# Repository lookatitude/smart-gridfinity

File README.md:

# Smart Gridfinity

**A smart storage system built on Gridfinity: it knows where every bin is, and it can point
to the one you need.**

[Gridfinity](https://gridfinity.xyz/) is an open, modular storage standard: a 42 mm grid of
baseplates and bins that you print yourself. Smart Gridfinity keeps that standard and adds
two things to it:

- **Location tracking.** Every bin carries a small ID chip. The base reads which bin stands
  on which cell, so the system always has a current map of your storage. Move a bin, or
  rearrange the whole grid, and the map follows without any setup.
- **Signalling.** Every compartment has a light under a clear floor. Ask your software, or
  an AI agent, for a part and the compartment that holds it lights up.

Around those two ideas the design aims for:

- **Bins that stay simple.** No battery, no radio and no processor in a bin. It gets power
  and data through four contacts in its foot, and works at any quarter turn.
- **A grid that grows.** Tiles snap together edge to edge and discover their neighbours.
  One power feed runs many tiles, flat on a desk or on a wall with magnets.
- **Optional smartness.** Plain Gridfinity bins and baseplates still fit and are included.
  Powered parts are an addition, not a requirement.
- **No soldering at the printed parts.** The circuit boards arrive assembled and plug or
  screw in.

Everything is open source: the OpenSCAD models, the circuit boards (KiCad, generated from
Python), and the checks that keep the two in agreement.

**Status: design stage.** The models, boards and checks agree with each other, but nothing
has been printed, no board has been ordered or reviewed by a person, and there is no
firmware or software yet.

## Explore

| Start here | |
|---|---|
| **[How it works](docs/how-it-works.md)** | The whole system explained with pictures, in about ten minutes |
| [Parts guide](docs/parts-guide.md) | Every printed part and board, which file makes it, how to print |
| [Status and open questions](docs/status.md) | What has been checked, and what has not |
| [Glossary](docs/glossary.md) | Tile, cell, row board, power cell and the rest |
| [Illustrated design page](https://lookatitude.github.io/smart-gridfinity/smart/design.html) | The full design on one page, with diagrams |
| [All documentation](docs/README.md) | Index by what you want to do |

## What is in the repository

| Folder | Contents |
|---|---|
| `lib/`, `parts/` | OpenSCAD sources: plain baseplates and bins, smart tiles, smart bins, power bin, drawer unit, jar sleeves, tile keys |
| `assembly.scad`, `assembly_smart.scad` | Assembled views used for the pictures |
| `pcb/` | The five circuit boards as KiCad files, generated by Python scripts. See [`pcb/README.md`](pcb/README.md) |
| `tests/` | Design checks: fit, contacts, power, grid layout. See [`tests/README.md`](tests/README.md) |
| `docs/` | Documentation, the materials list and the illustrated design page |
| `tools/` | Helper scripts: `make_intro_gif.sh` builds the animation above from `assembly_intro.scad` |

## The smart system in four lines

- Bins have no radio and no processor: a round board in the foot has four contact rings, an
  ID chip and a connector for the bin's lights.
- Under every row of cells in a tile sits one board with spring pins. The first row's board
  has the radio module and a 5 V converter; further rows are joined by short flat cables.
- A power bin on a starter tile feeds 12–24 V into the grid and talks to your network.
- Tiles are 2×2 to 4×4 cells and join with printed keys and edge connectors, without screws.

The full walk-through is in [How it works](docs/how-it-works.md).

## Build

Needs OpenSCAD 2021.01 or newer. Printable files go to `build/`, which is not in the repository.

    ./build.sh          # plain parts
    ./build_smart.sh    # smart parts

Sized for a 256 mm print bed.

Ready-made STL files are attached to the [releases](https://github.com/lookatitude/smart-gridfinity/releases). They are untested.

## Checks

Needs Python 3, OpenSCAD and, for the boards, KiCad 10.

    tests/run_all.sh    # contacts, power, grid layout, fit (the fit checks take over 10 minutes)

See `pcb/README.md` for the board checks.

## Licence

MIT. See `LICENSE`. This covers the OpenSCAD models, the scripts and the board designs.

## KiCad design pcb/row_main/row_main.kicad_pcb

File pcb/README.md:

# Circuit boards

Five boards, defined in Python and written out as KiCad 10 projects. All are drafts: they pass
KiCad's rule checks, but no person has reviewed them and none has been built.

| Board | Where it goes | Layers |
|---|---|---|
| `bin_board` | In the foot of each smart bin: four contact rings, ID chip, connector for the lights | 2 |
| `row_main` | Under the first row of a tile: spring pins for four cells, radio module, 5 V converter, switch chips, one flat-cable socket | 4 |
| `row_strip` | Under every further row: spring pins for four cells, one switch chip, two flat-cable sockets. Can be snapped shorter | 2 |
| `feed_board` | Under the power cell of a starter tile: four feed pins | 2 |
| `power_board` | Inside the power bin: DC input, fuse, hub radio | 4 |

## Contacts

Each cell has four spring pins in a line from the cell centre: ID at 0 mm, light data at
5.4 mm, 5 V at 9.2 mm, ground at 12.9 mm. The bin board has matching concentric rings, so a
bin works at any quarter turn.

Rows are joined by a flat cable: 12 conductors, 0.5 mm pitch, 30 mm long, contacts on the same
side at both ends. Positions 1–12: 5V, 5V, GND, GND, light data, GND, ID, select 0, select 1,
and three row-enable lines that shift by one on each strip.

## Regenerating

    python3 boards.py                 # schematics, parts lists, library tables
    python3 layout_bin.py             # bin_board layout
    python3 layout_contact.py         # feed_board layout
    python3 layout_rows.py strip      # row_strip layout
    python3 layout_rows.py main --keep   # row_main layout from the saved routing (row_main.ses)
    python3 layout_power.py place && python3 layout_power.py route --keep   # power_board
    python3 outputs.py                # rule checks, pictures, bom.csv, fab/ for every board

`row_main` and `power_board` are routed with Freerouting. Its results are not repeatable, so
the routing that passed is saved as a `.ses` file next to each board.

## Checks

`grid_limits.py` and `grid_power.py` model how far one power feed reaches across a grid.

    python3 check_rows.py    # row boards against the printed tile: outline, pins, holes, sockets
    python3 signals.py       # signal levels and timing through the switch chips

Each board folder holds `erc.rpt` and `drc.rpt` from the last run.

## Known limits

- The flat-cable sockets allow 0.7 A at 5 V per cable, so firmware must hold full white to
  11 lights behind any one cable.
- On `row_main` the 5 V copper narrows to 0.8 mm at the cable socket and runs on inner layers.
- `row_main` is checked at 0.125 mm track spacing, the other boards at 0.15 mm.
- Snapping a `row_strip` shorter cuts through 5 V and ground copper 0.7 mm apart. Untested.

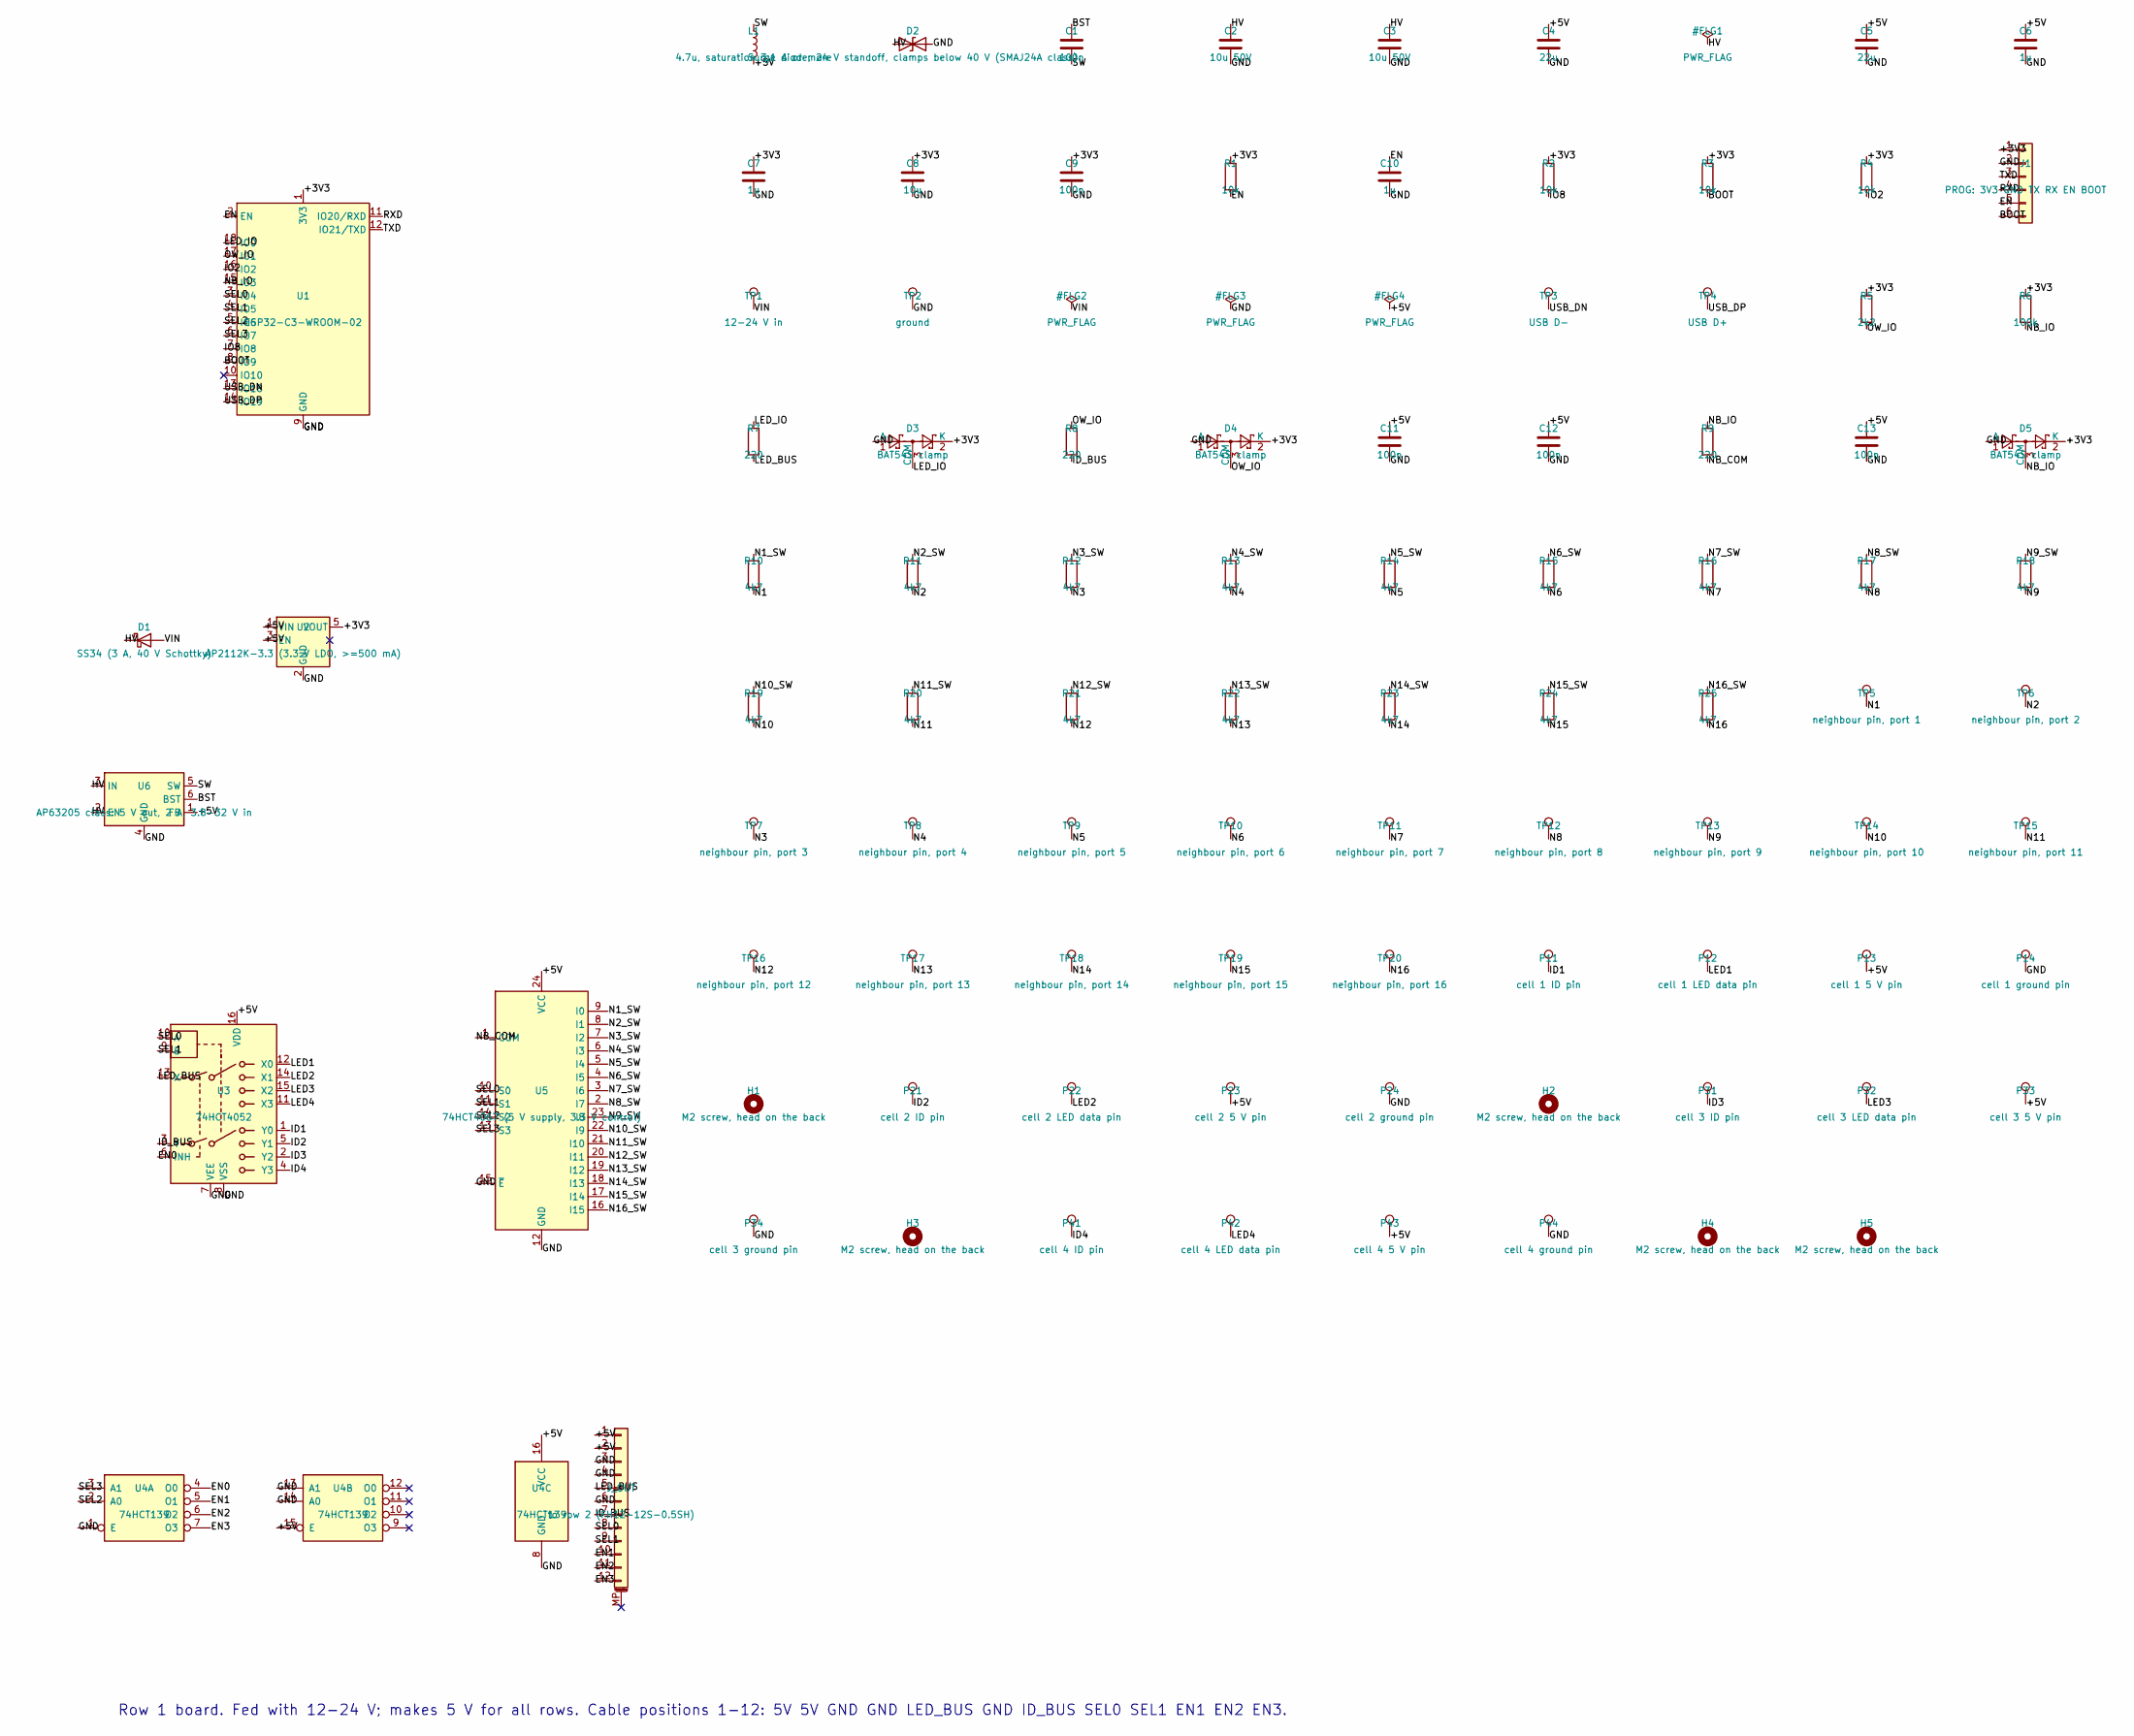
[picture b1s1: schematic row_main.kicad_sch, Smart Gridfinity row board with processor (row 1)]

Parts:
C1, C9, C11, C12, C13: 100n; C_0603_1608Metric
C2, C3: 10u 50V; C_1206_3216Metric
C4, C5: 22u; C_0805_2012Metric
C6, C7, C10: 1u; C_0603_1608Metric
C8: 10u; C_0805_2012Metric
D1: SS34 (3 A, 40 V Schottky); D_SMA
D2: Surge diode, 24 V standoff, clamps below 40 V (SM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; D_SMA
D3, D4, D5: BAT54S clamp; SOT-23
H1, H2, H3, H4, H5: M2 screw, head on the back; MountHole_M2_HeadBack
J1: PROG: 3V3 GND TX RX EN BOOT; WirePads_1x06_P1.5mm
J_OUT: to row 2 (FH12-12S-0.5SH); Hirose_FH12-12S-0.5SH_1x12-1MP_P0.50mm_Horizontal
L1: 4.7u, saturation 3.1 A or more; L_Bourns_SRP5030T
P11: cell 1 ID pin; SpringPin_MillMax0906
P12: cell 1 LED data pin; SpringPin_MillMax0906
P13: cell 1 5 V pin; SpringPin_MillMax0906
P14: cell 1 ground pin; SpringPin_MillMax0906
P21: cell 2 ID pin; SpringPin_MillMax0906
P22: cell 2 LED data pin; SpringPin_MillMax0906
P23: cell 2 5 V pin; SpringPin_MillMax0906
P24: cell 2 ground pin; SpringPin_MillMax0906
P31: cell 3 ID pin; SpringPin_MillMax0906
P32: cell 3 LED data pin; SpringPin_MillMax0906
P33: cell 3 5 V pin; SpringPin_MillMax0906
P34: cell 3 ground pin; SpringPin_MillMax0906
P41: cell 4 ID pin; SpringPin_MillMax0906
P42: cell 4 LED data pin; SpringPin_MillMax0906
P43: cell 4 5 V pin; SpringPin_MillMax0906
P44: cell 4 ground pin; SpringPin_MillMax0906
R1, R2, R3, R4: 10k; R_0603_1608Metric
R5: 2k2; R_0603_1608Metric
R6: 100k; R_0603_1608Metric
R7, R8, R9: 220; R_0603_1608Metric
R10, R11, R12, R13, R14, R15, R16, R17, R18, R19, R20, R21, R22, R23, R24, R25: 4k7; R_0603_1608Metric
TP1: 12-24 V in; WirePad_2.5
TP2: ground; WirePad_2.5
TP3: USB D-; WirePad_1.0
TP4: USB D+; WirePad_1.0
TP5: neighbour pin, port 1; WirePad_1.0
TP6: neighbour pin, port 2; WirePad_1.0
TP7: neighbour pin, port 3; WirePad_1.0
TP8: neighbour pin, port 4; WirePad_1.0
TP9: neighbour pin, port 5; WirePad_1.0
TP10: neighbour pin, port 6; WirePad_1.0
TP11: neighbour pin, port 7; WirePad_1.0
TP12: neighbour pin, port 8; WirePad_1.0
TP13: neighbour pin, port 9; WirePad_1.0
TP14: neighbour pin, port 10; WirePad_1.0
TP15: neighbour pin, port 11; WirePad_1.0
TP16: neighbour pin, port 12; WirePad_1.0
TP17: neighbour pin, port 13; WirePad_1.0
TP18: neighbour pin, port 14; WirePad_1.0
TP19: neighbour pin, port 15; WirePad_1.0
TP20: neighbour pin, port 16; WirePad_1.0
U1: ESP32-C3-WROOM-02
U2: AP2112K-3.3 (3.3 V LDO, >=500 mA); SOT-23-5
U3: 74HCT4052; TSSOP-16_4.4x5mm_P0.65mm
U4: 74HCT139; TSSOP-16_4.4x5mm_P0.65mm
U5: 74HCT4067 (5 V supply, 3.3 V control); TSSOP-24_4.4x7.8mm_P0.65mm
U6: AP63205 class: 5 V out, 2 A, 3.8-32 V in; TSOT-23-6

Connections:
+3V3: C7.1, C8.1, C9.1, D3.2 (K), D4.2 (K), D5.2 (K), J1.1, R1.1, R2.1, R3.1, R4.1, R5.1, R6.1, U1.1 (3V3), U2.5 (VOUT)
+5V: C4.1, C5.1, C6.1, C11.1, C12.1, C13.1, J_OUT.1, J_OUT.2, L1.2, P13.1, P23.1, P33.1, P43.1, U2.1 (VIN), U2.3 (EN), U3.16 (VDD), U4.15 (E), U4.16 (VCC), U5.24 (VCC), U6.1 (FB)
BOOT: J1.6, R3.2, U1.8 (IO9)
BST: C1.1, U6.6 (BST)
EN: C10.1, J1.5, R1.2, U1.2 (EN)
EN0: U3.6 (INH), U4.4 (O0)
EN1: J_OUT.10, U4.5 (O1)
EN2: J_OUT.11, U4.6 (O2)
EN3: J_OUT.12, U4.7 (O3)
GND: C2.2, C3.2, C4.2, C5.2, C6.2, C7.2, C8.2, C9.2, C10.2, C11.2, C12.2, C13.2, D2.2 (A2), D3.1 (A), D4.1 (A), D5.1 (A), J1.2, J_OUT.3, J_OUT.4, J_OUT.6, P14.1, P24.1, P34.1, P44.1, TP2.1, U1.9 (GND), U1.19 (GND), U2.2 (GND), U3.7 (VEE), U3.8 (VSS), U4.1 (E), U4.8 (GND), U4.13 (A1), U4.14 (A0), U5.12 (GND), U5.15 (~E), U6.4 (GND)
HV: C2.1, C3.1, D1.1 (K), D2.1 (A1), U6.2 (EN), U6.3 (IN)
ID1: P11.1, U3.1 (Y0)
ID2: P21.1, U3.5 (Y1)
ID3: P31.1, U3.2 (Y2)
ID4: P41.1, U3.4 (Y3)
ID_BUS: J_OUT.7, R8.2, U3.3 (Y)
IO2: R4.2, U1.16 (IO2)
IO8: R2.2, U1.7 (IO8)
LED1: P12.1, U3.12 (X0)
LED2: P22.1, U3.14 (X1)
LED3: P32.1, U3.15 (X2)
LED4: P42.1, U3.11 (X3)
LED_BUS: J_OUT.5, R7.2, U3.13 (X)
LED_IO: D3.3 (COM), R7.1, U1.18 (IO0)
N1: R10.2, TP5.1
N1_SW: R10.1, U5.9 (I0)
N2: R11.2, TP6.1
N2_SW: R11.1, U5.8 (I1)
N3: R12.2, TP7.1
N3_SW: R12.1, U5.7 (I2)
N4: R13.2, TP8.1
N4_SW: R13.1, U5.6 (I3)
N5: R14.2, TP9.1
N5_SW: R14.1, U5.5 (I4)
N6: R15.2, TP10.1
N6_SW: R15.1, U5.4 (I5)
N7: R16.2, TP11.1
N7_SW: R16.1, U5.3 (I6)
N8: R17.2, TP12.1
N8_SW: R17.1, U5.2 (I7)
N9: R18.2, TP13.1
N9_SW: R18.1, U5.23 (I8)
N10: R19.2, TP14.1
N10_SW: R19.1, U5.22 (I9)
N11: R20.2, TP15.1
N11_SW: R20.1, U5.21 (I10)
N12: R21.2, TP16.1
N12_SW: R21.1, U5.20 (I11)
N13: R22.2, TP17.1
N13_SW: R22.1, U5.19 (I12)
N14: R23.2, TP18.1
N14_SW: R23.1, U5.18 (I13)
N15: R24.2, TP19.1
N15_SW: R24.1, U5.17 (I14)
N16: R25.2, TP20.1
N16_SW: R25.1, U5.16 (I15)
NB_COM: R9.2, U5.1 (COM)
NB_IO: D5.3 (COM), R6.2, R9.1, U1.15 (IO3)
OW_IO: D4.3 (COM), R5.2, R8.1, U1.17 (IO1)
RXD: J1.4, U1.11 (IO20/RXD)
SEL0: J_OUT.8, U1.3 (IO4), U3.10 (A), U5.10 (S0)
SEL1: J_OUT.9, U1.4 (IO5), U3.9 (B), U5.11 (S1)
SEL2: U1.5 (IO6), U4.2 (A0), U5.14 (S2)
SEL3: U1.6 (IO7), U4.3 (A1), U5.13 (S3)
SW: C1.2, L1.1, U6.5 (SW)
TXD: J1.3, U1.12 (IO21/TXD)
USB_DN: TP3.1, U1.13 (IO18)
USB_DP: TP4.1, U1.14 (IO19)
VIN: D1.2 (A), TP1.1

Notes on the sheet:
Row 1 board. Fed with 12-24 V; makes 5 V for all rows. Cable positions 1-12: 5V 5V GND GND LED_BUS GND ID_BUS SEL0 SEL1 EN1 EN2 EN3.

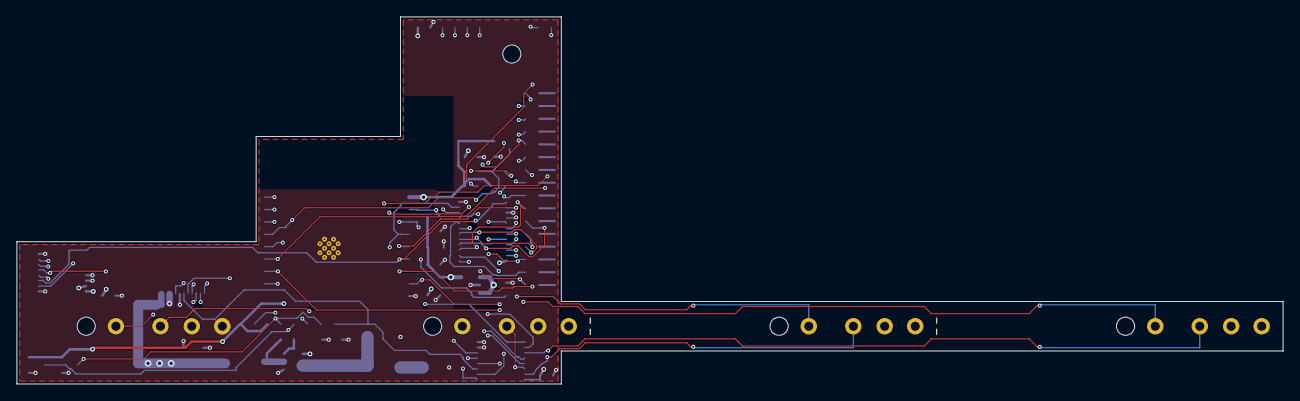
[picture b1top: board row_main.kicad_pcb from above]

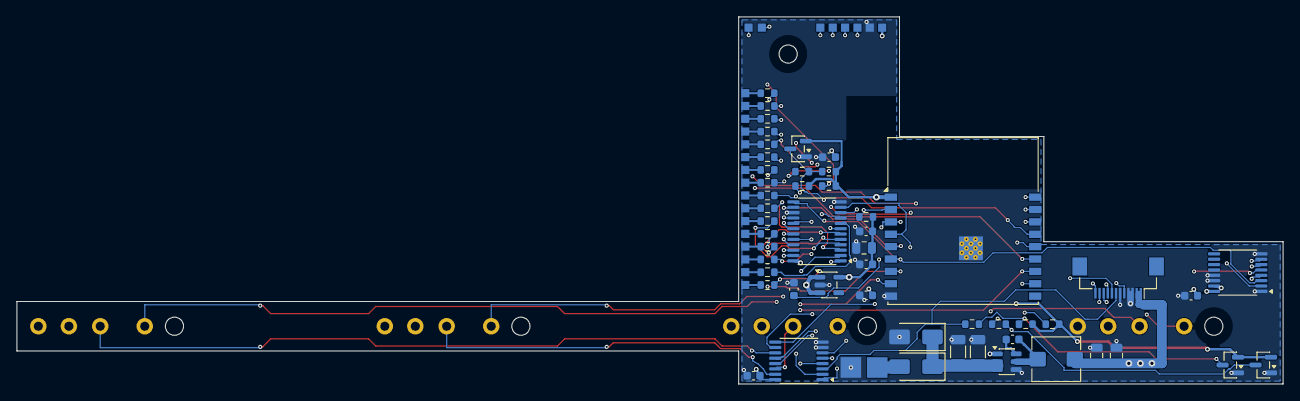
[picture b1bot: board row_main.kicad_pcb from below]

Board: 4 copper layers, 153.5 x 44.5 mm, 93 parts (72 on the bottom side), 69 nets.

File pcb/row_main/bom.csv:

Qty,Value,Footprint,References
5,100n,C_0603_1608Metric,C1 C11 C12 C13 C9
1,10u,C_0805_2012Metric,C8
2,10u 50V,C_1206_3216Metric,C2 C3
3,1u,C_0603_1608Metric,C10 C6 C7
2,22u,C_0805_2012Metric,C4 C5
3,BAT54S clamp,SOT-23,D3 D4 D5
1,"SS34 (3 A, 40 V Schottky)",D_SMA,D1
1,"Surge diode, 24 V standoff, clamps below 40 V (SMAJ24A class)",D_SMA,D2
1,"Hirose FH12-12S-0.5SH flat-cable socket, 12-way 0.5 mm, bottom contact",Hirose_FH12-12S-0.5SH_1x12-1MP_P0.50mm_Horizontal,J_OUT
1,"4.7u, saturation 3.1 A or more",L_Bourns_SRP5030T,L1
16,"Spring pin with solder tail, Mill-Max 0906 class, 2 A",SpringPin_MillMax0906,P11 P12 P13 P14 P21 P22 P23 P24 P31 P32 P33 P34 P41 P42 P43 P44
1,100k,R_0603_1608Metric,R6
4,10k,R_0603_1608Metric,R1 R2 R3 R4
3,220,R_0603_1608Metric,R7 R8 R9
1,2k2,R_0603_1608Metric,R5
16,4k7,R_0603_1608Metric,R10 R11 R12 R13 R14 R15 R16 R17 R18 R19 R20 R21 R22 R23 R24 R25
1,74HCT139,TSSOP-16_4.4x5mm_P0.65mm,U4
1,74HCT4052,TSSOP-16_4.4x5mm_P0.65mm,U3
1,"74HCT4067 (5 V supply, 3.3 V control)",TSSOP-24_4.4x7.8mm_P0.65mm,U5
1,"AP2112K-3.3 (3.3 V LDO, >=500 mA)",SOT-23-5,U2
1,"AP63205 class: 5 V out, 2 A, 3.8-32 V in",TSOT-23-6,U6
1,ESP32-C3-WROOM-02,ESP32-C3-WROOM-02,U1

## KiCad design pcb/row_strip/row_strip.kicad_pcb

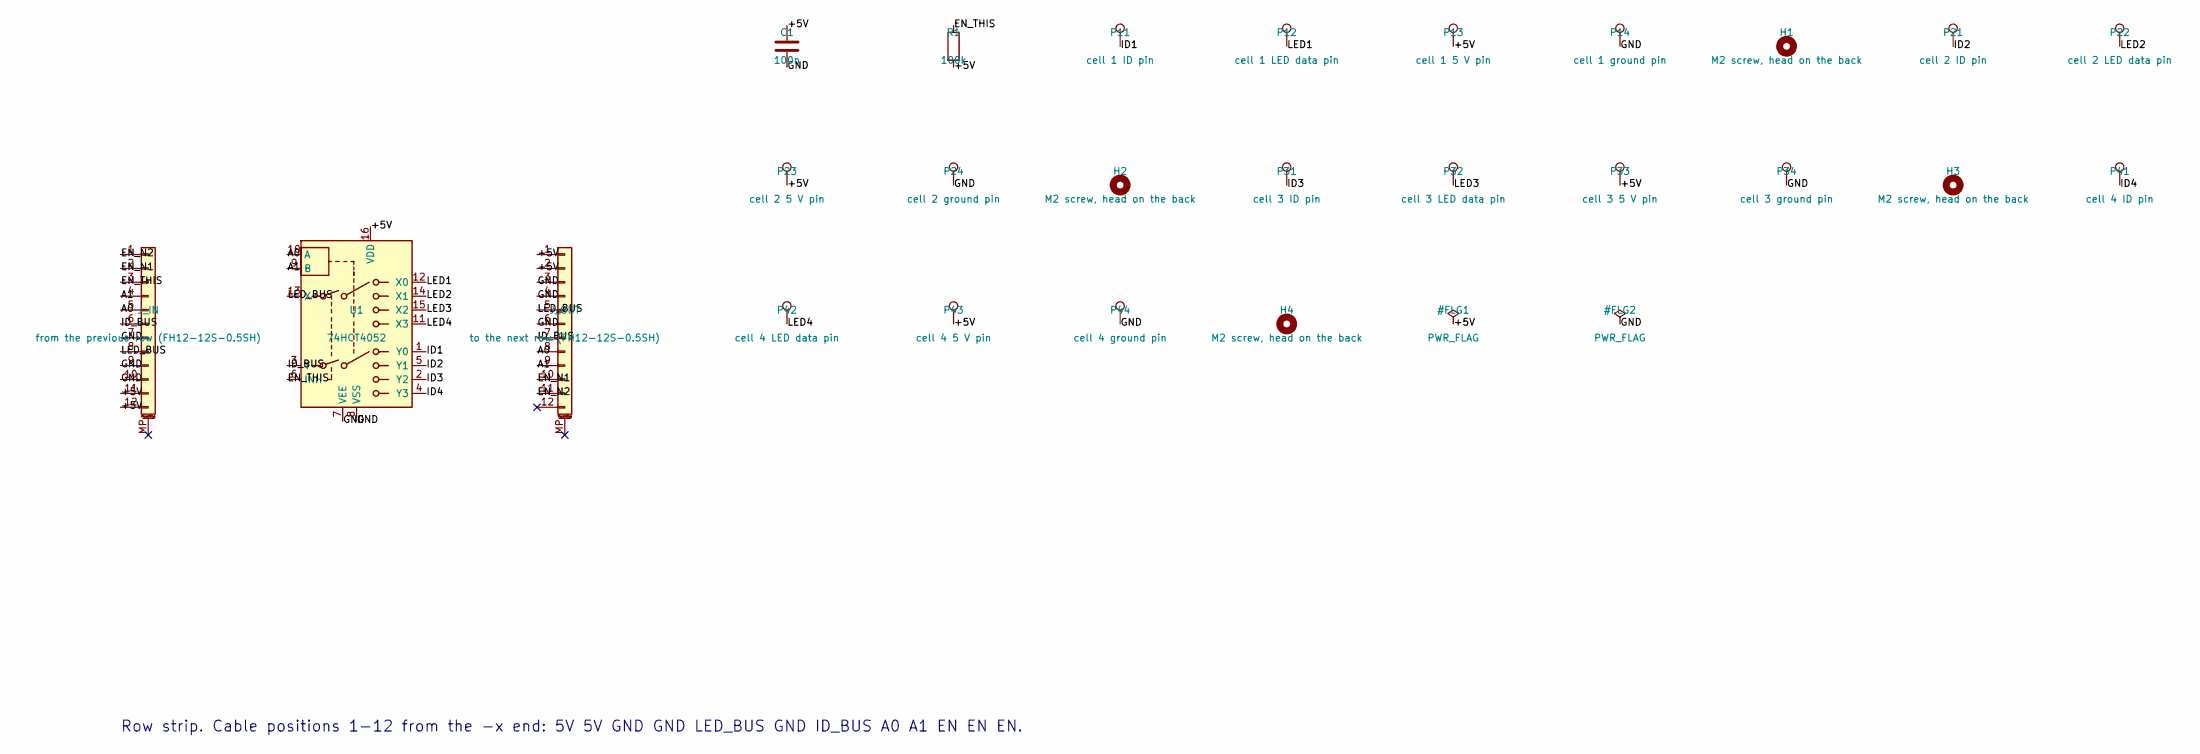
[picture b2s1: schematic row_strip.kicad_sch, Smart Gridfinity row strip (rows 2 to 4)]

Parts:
C1: 100n; C_0603_1608Metric
H1, H2, H3, H4: M2 screw, head on the back; MountHole_M2_HeadBack
J_IN: from the previous row (FH12-12S-0.5SH); Hirose_FH12-12S-0.5SH_1x12-1MP_P0.50mm_Horizontal
J_OUT: to the next row (FH12-12S-0.5SH); Hirose_FH12-12S-0.5SH_1x12-1MP_P0.50mm_Horizontal
P11: cell 1 ID pin; SpringPin_MillMax0906
P12: cell 1 LED data pin; SpringPin_MillMax0906
P13: cell 1 5 V pin; SpringPin_MillMax0906
P14: cell 1 ground pin; SpringPin_MillMax0906
P21: cell 2 ID pin; SpringPin_MillMax0906
P22: cell 2 LED data pin; SpringPin_MillMax0906
P23: cell 2 5 V pin; SpringPin_MillMax0906
P24: cell 2 ground pin; SpringPin_MillMax0906
P31: cell 3 ID pin; SpringPin_MillMax0906
P32: cell 3 LED data pin; SpringPin_MillMax0906
P33: cell 3 5 V pin; SpringPin_MillMax0906
P34: cell 3 ground pin; SpringPin_MillMax0906
P41: cell 4 ID pin; SpringPin_MillMax0906
P42: cell 4 LED data pin; SpringPin_MillMax0906
P43: cell 4 5 V pin; SpringPin_MillMax0906
P44: cell 4 ground pin; SpringPin_MillMax0906
R1: 100k; R_0603_1608Metric
U1: 74HCT4052; TSSOP-16_4.4x5mm_P0.65mm

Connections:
+5V: C1.1, J_IN.11, J_IN.12, J_OUT.1, J_OUT.2, P13.1, P23.1, P33.1, P43.1, R1.2, U1.16 (VDD)
A0: J_IN.5, J_OUT.8, U1.10 (A)
A1: J_IN.4, J_OUT.9, U1.9 (B)
EN_N1: J_IN.2, J_OUT.10
EN_N2: J_IN.1, J_OUT.11
EN_THIS: J_IN.3, R1.1, U1.6 (INH)
GND: C1.2, J_IN.7, J_IN.9, J_IN.10, J_OUT.3, J_OUT.4, J_OUT.6, P14.1, P24.1, P34.1, P44.1, U1.7 (VEE), U1.8 (VSS)
ID1: P11.1, U1.1 (Y0)
ID2: P21.1, U1.5 (Y1)
ID3: P31.1, U1.2 (Y2)
ID4: P41.1, U1.4 (Y3)
ID_BUS: J_IN.6, J_OUT.7, U1.3 (Y)
LED1: P12.1, U1.12 (X0)
LED2: P22.1, U1.14 (X1)
LED3: P32.1, U1.15 (X2)
LED4: P42.1, U1.11 (X3)
LED_BUS: J_IN.8, J_OUT.5, U1.13 (X)

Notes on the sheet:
Row strip. Cable positions 1-12 from the -x end: 5V 5V GND GND LED_BUS GND ID_BUS A0 A1 EN EN EN.

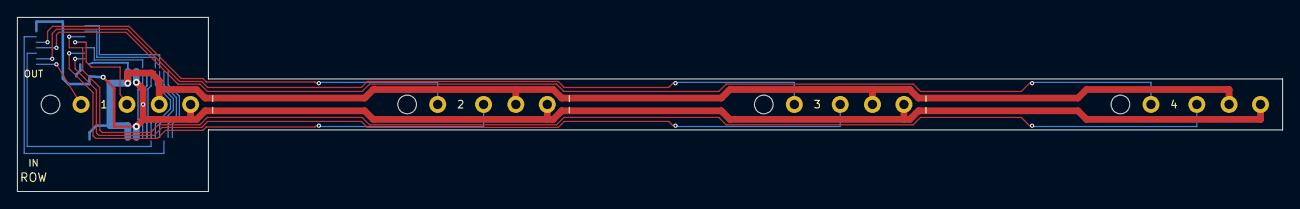
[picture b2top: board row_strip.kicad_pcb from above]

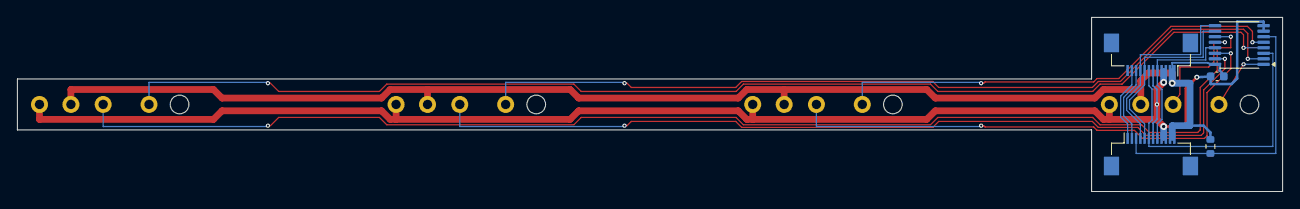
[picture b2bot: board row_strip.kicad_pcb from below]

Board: 2 copper layers, 149.0 x 20.5 mm, 25 parts (5 on the bottom side), 17 nets.

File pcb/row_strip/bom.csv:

Qty,Value,Footprint,References
1,100n,C_0603_1608Metric,C1
2,"Hirose FH12-12S-0.5SH flat-cable socket, 12-way 0.5 mm, bottom contact",Hirose_FH12-12S-0.5SH_1x12-1MP_P0.50mm_Horizontal,J_IN J_OUT
16,"Spring pin with solder tail, Mill-Max 0906 class, 2 A",SpringPin_MillMax0906,P11 P12 P13 P14 P21 P22 P23 P24 P31 P32 P33 P34 P41 P42 P43 P44
1,100k,R_0603_1608Metric,R1
1,74HCT4052,TSSOP-16_4.4x5mm_P0.65mm,U1

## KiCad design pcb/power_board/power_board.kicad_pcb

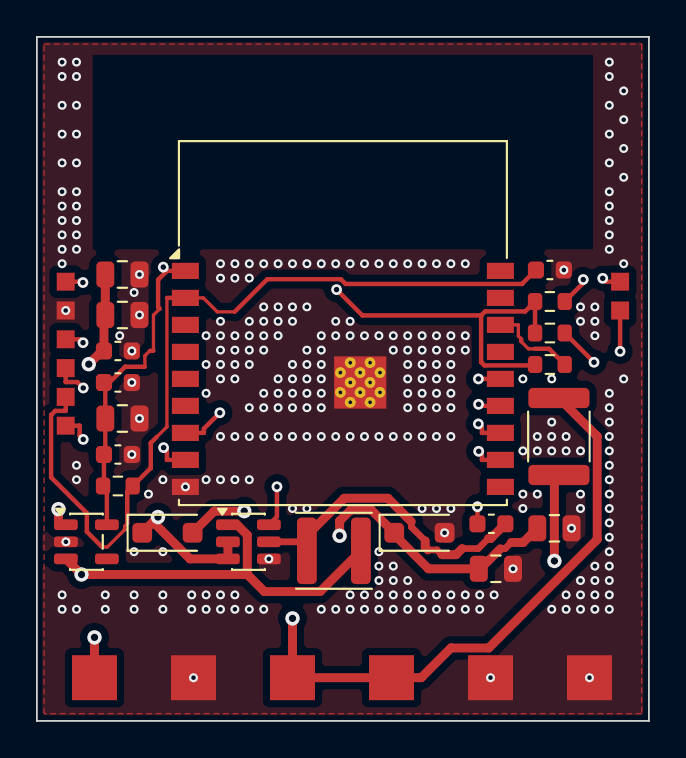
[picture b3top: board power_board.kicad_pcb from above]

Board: 4 copper layers, 34.0 x 38.0 mm, 35 parts (0 on the bottom side), 16 nets.

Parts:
C1, C9: 100n; C_0603_1608Metric
C2, C3: 10u 50V; C_0805_2012Metric
C4, C5: 22u; C_0805_2012Metric
C6, C7, C10: 1u; C_0603_1608Metric
C8: 10u; C_0805_2012Metric
D1: SS34 (3 A, 40 V Schottky); D_SOD-123F
D2: Surge diode, 24 V standoff, clamps below 40 V (SM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; D_SOD-123F
DC+: DC_IN; WirePad_2.5
DC-: GND; WirePad_2.5
F1: PTC 3 A hold, 30 V; Fuse_1812_4532Metric
FEED+1, FEED+2: VIN; WirePad_2.5
FEED-1, FEED-2: GND; WirePad_2.5
L1: 4.7u, saturation 3.1 A or more; L_APV_ANR4030
PG1: +3V3; WirePad_1.0
PG2: GND; WirePad_1.0
PG3: TXD; WirePad_1.0
PG4: RXD; WirePad_1.0
PG5: EN; WirePad_1.0
PG6: BOOT; WirePad_1.0
R1, R2, R3, R4: 10k; R_0603_1608Metric
U1: ESP32-C3-WROOM-02
U2: AP2112K-3.3 (3.3 V LDO, >=500 mA); SOT-23-5
U6: AP63205 class: 5 V out, 2 A, 3.8-32 V in; TSOT-23-6
USB1: USB_DN; WirePad_1.0
USB2: USB_DP; WirePad_1.0

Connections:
+3V3: C7.1, C8.1, C9.1, PG1.1, R1.1, R2.1, R3.1, R4.1, U1.1, U2.5
+5V: C4.1, C5.1, C6.1, L1.2, U2.1, U2.3, U6.1
BOOT: PG6.1, R3.2, U1.8
BST: C1.1, U6.6
DC_IN: DC+.1, F1.1
EN: C10.1, PG5.1, R1.2, U1.2
GND: C2.2, C3.2, C4.2, C5.2, C6.2, C7.2, C8.2, C9.2, C10.2, D2.2, DC-.1, FEED-1.1, FEED-2.1, PG2.1, U1.9, U1.19, U2.2, U6.4
HV: C2.1, C3.1, D1.1, D2.1, U6.2, U6.3
IO2: R4.2, U1.16
IO8: R2.2, U1.7
RXD: PG4.1, U1.11
SW: C1.2, L1.1, U6.5
TXD: PG3.1, U1.12
USB_DN: U1.13, USB1.1
USB_DP: U1.14, USB2.1
VIN: D1.2, F1.2, FEED+1.1, FEED+2.1

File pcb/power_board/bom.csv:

Qty,Value,Footprint,References
2,100n,C_0603_1608Metric,C1 C9
1,10u,C_0805_2012Metric,C8
2,10u 50V,C_0805_2012Metric,C2 C3
3,1u,C_0603_1608Metric,C10 C6 C7
2,22u,C_0805_2012Metric,C4 C5
1,"SS34 (3 A, 40 V Schottky)",D_SOD-123F,D1
1,"Surge diode, 24 V standoff, clamps below 40 V (SMAJ24A class)",D_SOD-123F,D2
1,"PTC 3 A hold, 30 V",Fuse_1812_4532Metric,F1
1,"4.7u, saturation 3.1 A or more",L_APV_ANR4030,L1
4,10k,R_0603_1608Metric,R1 R2 R3 R4
1,"AP2112K-3.3 (3.3 V LDO, >=500 mA)",SOT-23-5,U2
1,"AP63205 class: 5 V out, 2 A, 3.8-32 V in",TSOT-23-6,U6
1,ESP32-C3-WROOM-02,ESP32-C3-WROOM-02,U1

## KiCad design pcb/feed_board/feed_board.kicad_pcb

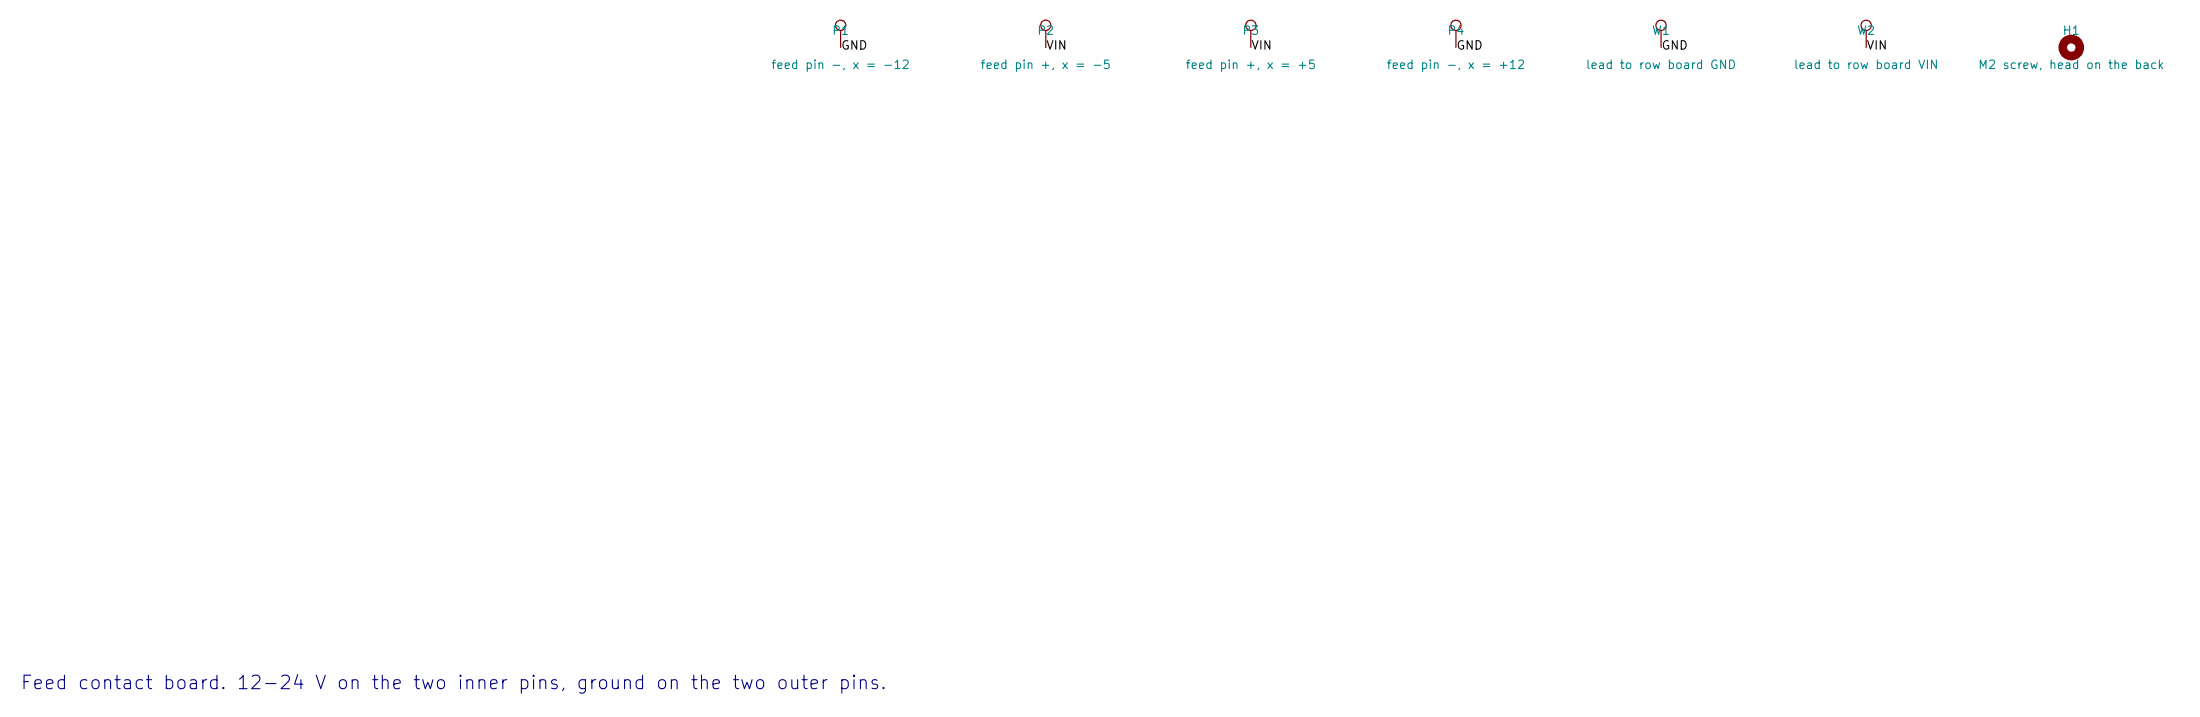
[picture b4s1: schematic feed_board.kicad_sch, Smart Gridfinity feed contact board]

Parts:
H1: M2 screw, head on the back; MountHole_M2_HeadBack
P1: feed pin -, x = -12; SpringPin_MillMax0906
P2: feed pin +, x = -5; SpringPin_MillMax0906
P3: feed pin +, x = +5; SpringPin_MillMax0906
P4: feed pin -, x = +12; SpringPin_MillMax0906
W1: lead to row board GND; WirePad_2.5
W2: lead to row board VIN; WirePad_2.5

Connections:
GND: P1.1, P4.1, W1.1
VIN: P2.1, P3.1, W2.1

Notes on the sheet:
Feed contact board. 12-24 V on the two inner pins, ground on the two outer pins.

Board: 2 copper layers, 7 parts (2 on the bottom side), 2 nets, no tracks yet.

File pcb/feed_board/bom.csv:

Qty,Value,Footprint,References
4,"Spring pin with solder tail, Mill-Max 0906 class, 2 A",SpringPin_MillMax0906,P1 P2 P3 P4

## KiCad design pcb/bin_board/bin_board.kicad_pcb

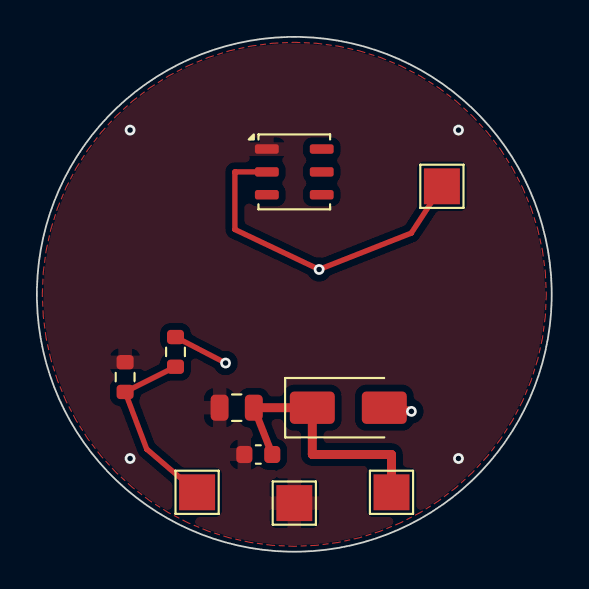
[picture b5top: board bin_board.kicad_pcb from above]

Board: 2 copper layers, 28.6 x 28.6 mm, 11 parts (1 on the bottom side), 6 nets.

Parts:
C1: 10u; C_0805_2012Metric
C2: 100n; C_0603_1608Metric
D1: SS14; D_SMA
J1A: LED data; TestPoint_Pad_2.0x2.0mm
J1B: LED gnd; TestPoint_Pad_2.0x2.0mm
J1C: LED 5V; TestPoint_Pad_2.0x2.0mm
R1: 100; R_0603_1608Metric
R2: 100k; R_0603_1608Metric
RING1: contact rings; ContactRings
TP5: ID foot 2; TestPoint_Pad_2.0x2.0mm
U1: DS2431P; TSOC-6_3.76x3.94mm_P1.27mm

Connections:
+5V: C1.1, C2.1, D1.1, J1C.1
DATA: R1.1, RING1.2
GND: C1.2, C2.2, J1B.1, R2.2, RING1.4, U1.1
ID: RING1.1, TP5.1, U1.2
LED_DIN: J1A.1, R1.2, R2.1
VIN: D1.2, RING1.3

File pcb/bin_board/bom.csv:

Qty,Value,Footprint,References
1,100n,C_0603_1608Metric,C2
1,10u,C_0805_2012Metric,C1
1,SS14,D_SMA,D1
1,100,R_0603_1608Metric,R1
1,100k,R_0603_1608Metric,R2
1,DS2431P,TSOC-6_3.76x3.94mm_P1.27mm,U1
